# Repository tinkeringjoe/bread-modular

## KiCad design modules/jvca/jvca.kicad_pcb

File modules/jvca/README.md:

# JVCA

JFET based VCA with bias and gain control.

## Usage

* We can control CV gain with the "CV GAIN" RV and minumum gain is 0.05 and maximum is 1.
* CV bias RV will change the CV bias from 1V to 3V range.
  * If it's 1V, audio is audible even with CV change.
  * If it's 3V, audio is not audible

* If we center the CV around 2V, 500mv amplitude is enough to cut through the audio.
* But we can play with these values to get interesting results

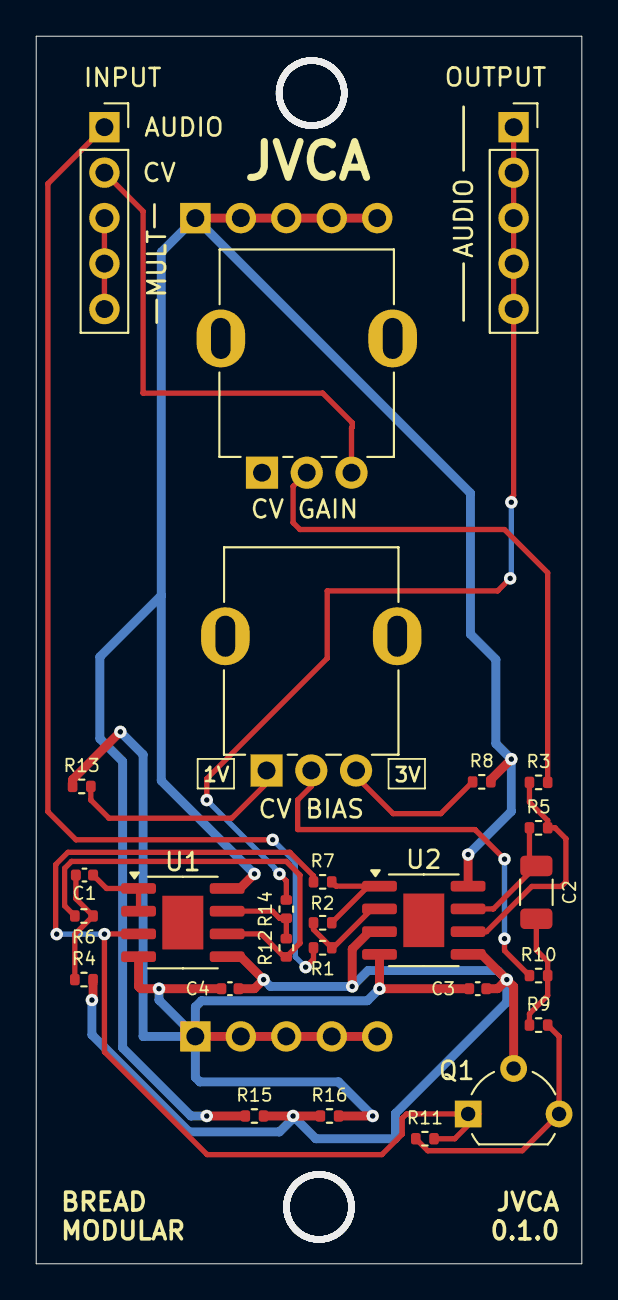
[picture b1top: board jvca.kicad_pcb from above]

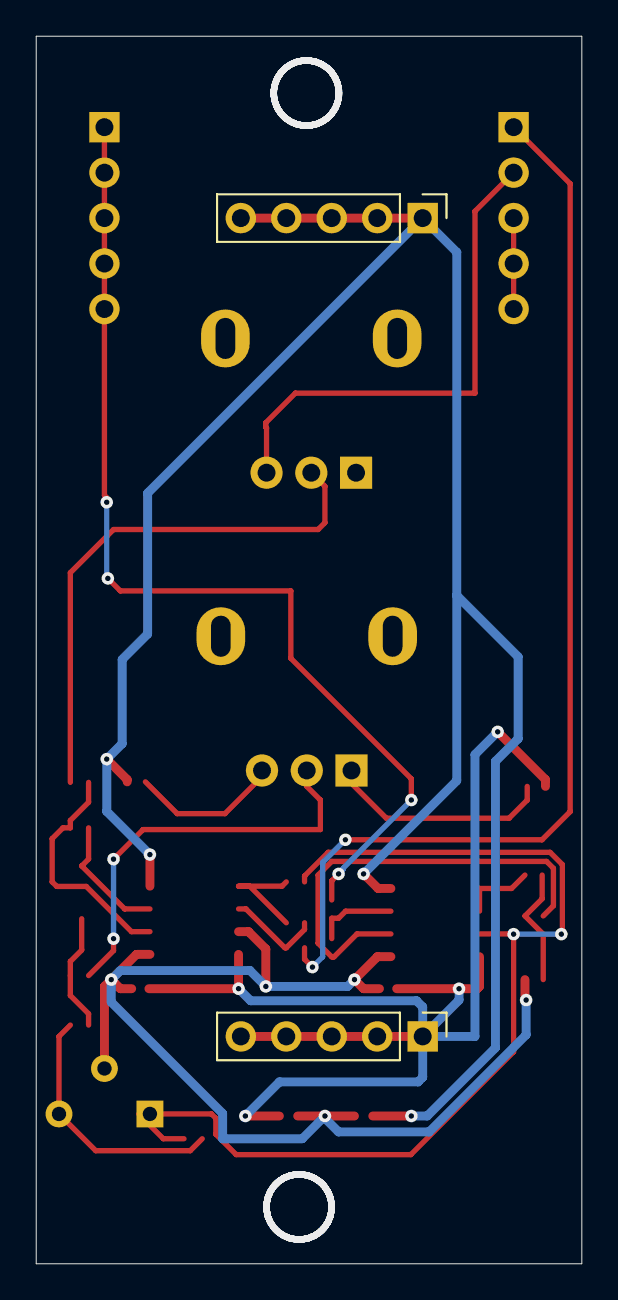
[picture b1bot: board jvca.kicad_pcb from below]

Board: 2 copper layers, 30.5 x 68.6 mm, 29 parts (2 on the bottom side), 22 nets.

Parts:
5V1: Conn_01x05_Pin; PinHeader_1x05_P2.54mm_Vertical
C1, C3, C4: 0.1uf; C_0402_1005Metric
C2: 4.7uf; C_1206_3216Metric
CV BIAS: 1k; Potentiometer_RV09
CV GAIN: 1M; Potentiometer_RV09
GND1: Conn_01x05_Pin; PinHeader_1x05_P2.54mm_Vertical
INPUT: Conn_01x05_Socket; PinSocket_1x05_P2.54mm_Vertical
OUTPUT: Conn_01x05_Socket; PinSocket_1x05_P2.54mm_Vertical
Q1: 2N5457; TO-92L_Wide
R1, R12: 200k; R_0402_1005Metric
R2, R6: 22k; R_0402_1005Metric
R3, R5: 51k; R_0402_1005Metric
R4, R7, R10: 100k; R_0402_1005Metric
R8: 2k; R_0402_1005Metric
R9, R11: 1M; R_0402_1005Metric
R13, R14, R15, R16: 1k; R_0402_1005Metric
U1, U2: MCP6002-xSN; SOIC-8-1EP_3.9x4.9mm_P1.27mm_EP2.29x3mm

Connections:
+2.5V: C3.2, C4.2, Q1.2 (S), R4.2, R15.2, R16.1, U1.5 (+), U2.3 (+), U2.5 (+)
+5V: 5V1.1, 5V1.2, 5V1.3, 5V1.4, 5V1.5, R8.2, R15.1, U1.8 (V+), U2.8 (V+)
CV: CV GAIN.3, INPUT.2
GND: C3.1, C4.1, GND1.1, GND1.2, GND1.3, GND1.4, GND1.5, R13.1, R16.2, U1.4 (V-), U2.4 (V-)
JFET_CV: C2.2, R9.1, R10.2
JFET_OUT: Q1.1 (D), R7.1, R11.2, U1.3 (+)
unnamed: C1.2, R4.1, R6.1
unnamed: C2.1, R5.1, U2.7
unnamed: INPUT.3, INPUT.4, INPUT.5
unnamed: Q1.3 (G), R9.2, R11.1
unnamed: R2.1, R7.2, U2.1
unnamed: CV GAIN.2, R3.2
unnamed: CV BIAS.3, R8.1
unnamed: CV BIAS.2, R10.1
unnamed: R12.2, R14.1, U1.7
unnamed: CV BIAS.1, R13.2
unnamed: C1.1, U1.1, U1.2 (-)
unnamed: R6.2, R12.1, U1.6 (-)
unnamed: R1.1, R2.2, U2.2 (-)
unnamed: R3.1, R5.2, U2.6 (-)
V_IN: INPUT.1, R1.2
V_OUT: OUTPUT.1, OUTPUT.2, OUTPUT.3, OUTPUT.4, OUTPUT.5, R14.2

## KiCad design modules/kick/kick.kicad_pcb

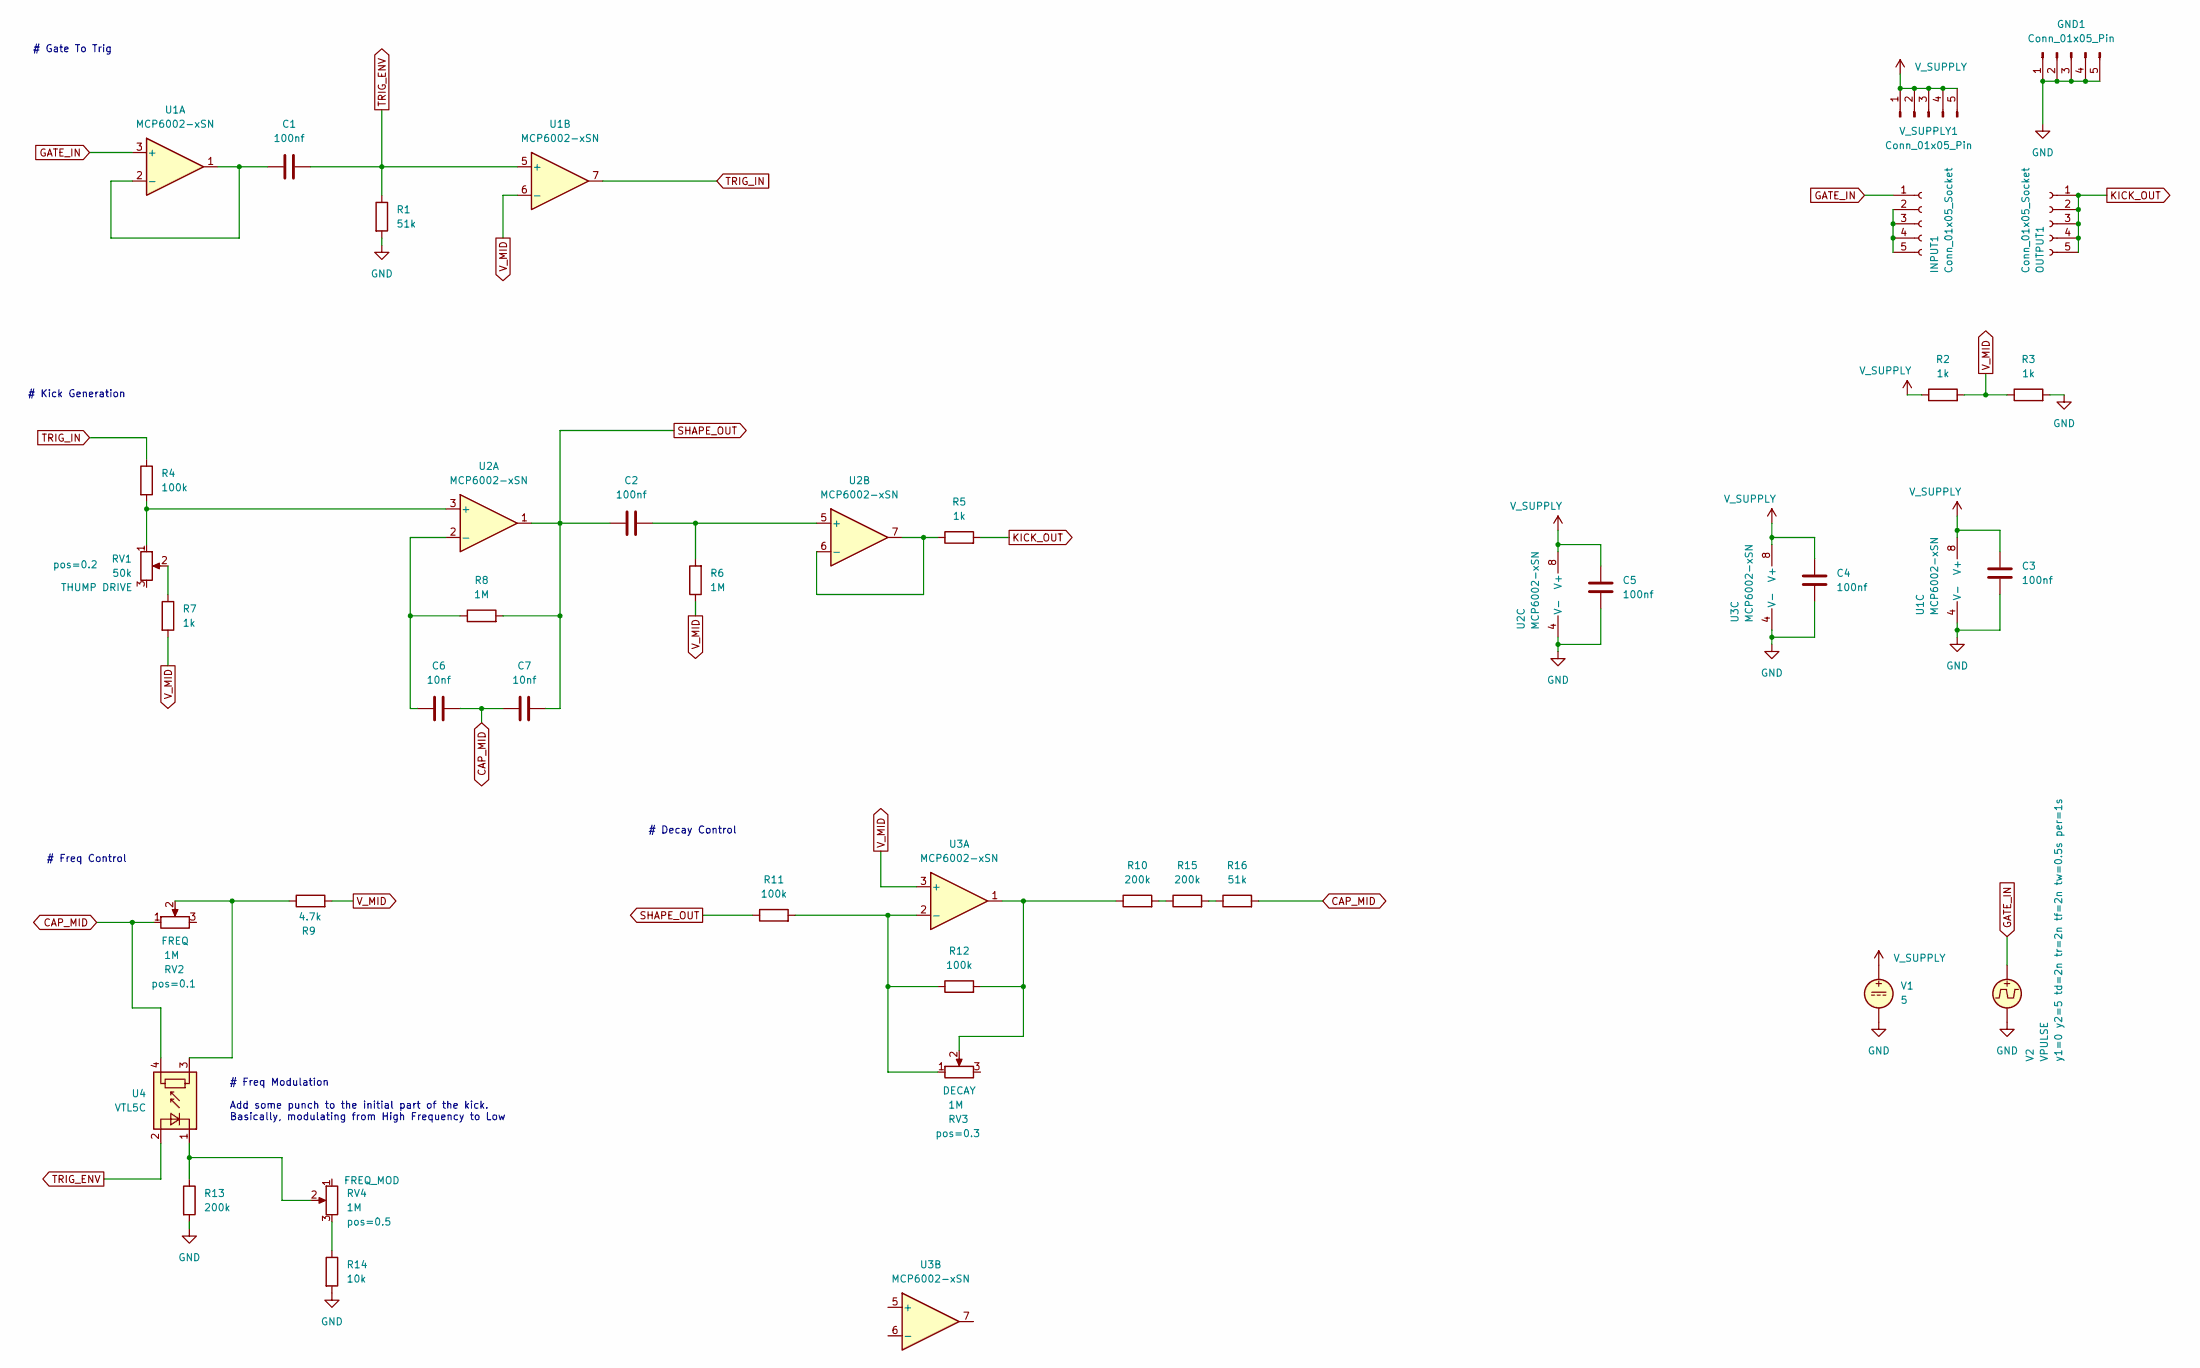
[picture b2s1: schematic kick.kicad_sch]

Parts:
C1, C2, C3, C4, C5: 100nf; C_0402_1005Metric
C6, C7: 10nf; C_0402_1005Metric
GND1: Conn_01x05_Pin; Power_Connector
INPUT1: Conn_01x05_Socket; PinSocket_1x05_P2.54mm_Vertical
OUTPUT1: Conn_01x05_Socket; PinSocket_1x05_P2.54mm_Vertical
R1, R16: 51k; R_0402_1005Metric
R2, R3, R5, R7: 1k; R_0402_1005Metric
R4, R11, R12: 100k; R_0402_1005Metric
R6, R8: 1M; R_0402_1005Metric
R9: 4.7k; R_0402_1005Metric
R10, R13, R15: 200k; R_0402_1005Metric
R14: 10k; R_0402_1005Metric
RV1: 50k; Potentiometer_RV09
RV2, RV3, RV4: 1M; Potentiometer_RV09
U1, U2, U3: MCP6002-xSN; SOIC-8-1EP_3.9x4.9mm_P1.27mm_EP2.29x3mm
U4: VTL5C
V1: 5
V2: VPULSE
V_SUPPLY1: Conn_01x05_Pin; Power_Connector

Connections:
CAP_MID: C6.2, C7.1, R16.2, RV2.1, U4.4
GATE_IN: INPUT1.1, U1.3 (+), V2.1
GND: C3.2, C4.2, C5.2, GND1.1, GND1.2, GND1.3, GND1.4, GND1.5, R1.2, R3.2, R13.2, R14.2, U1.4 (V-), U2.4 (V-), U3.4 (V-), V1.2, V2.2
KICK_OUT: OUTPUT1.1, OUTPUT1.2, OUTPUT1.3, OUTPUT1.4, OUTPUT1.5, R5.2
unnamed: INPUT1.2, INPUT1.3, INPUT1.4, INPUT1.5
unnamed: R7.1, RV1.2
unnamed: R9.1, RV2.2, U4.3
unnamed: R10.1, R12.2, RV3.2, U3.1
unnamed: R10.2, R15.1
unnamed: R14.1, RV4.3
unnamed: R15.2, R16.1
unnamed: C1.1, U1.1, U1.2 (-)
unnamed: R4.2, RV1.1, U2.3 (+)
unnamed: C6.1, R8.1, U2.2 (-)
unnamed: C2.2, R6.2, U2.5 (+)
unnamed: R5.1, U2.6 (-), U2.7
unnamed: R11.2, R12.1, RV3.1, U3.2 (-)
unnamed: R13.1, RV4.2, U4.1 (-)
SHAPE_OUT: C2.1, C7.2, R8.2, R11.1, U2.1
TRIG_ENV: C1.2, R1.1, U1.5 (+), U4.2 (+)
TRIG_IN: R4.1, U1.7
V_MID: R2.2, R3.1, R6.1, R7.2, R9.2, U1.6 (-), U3.3 (+)
V_SUPPLY: C3.1, C4.1, C5.1, R2.1, U1.8 (V+), U2.8 (V+), U3.8 (V+), V1.1, V_SUPPLY1.1, V_SUPPLY1.2, V_SUPPLY1.3, V_SUPPLY1.4, V_SUPPLY1.5

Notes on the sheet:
# Decay Control
# Gate To Trig
# Freq Control
# Kick Generation
# Freq Modulation Add some punch to the initial part of the kick. Basically, modulating from High Frequency to Low

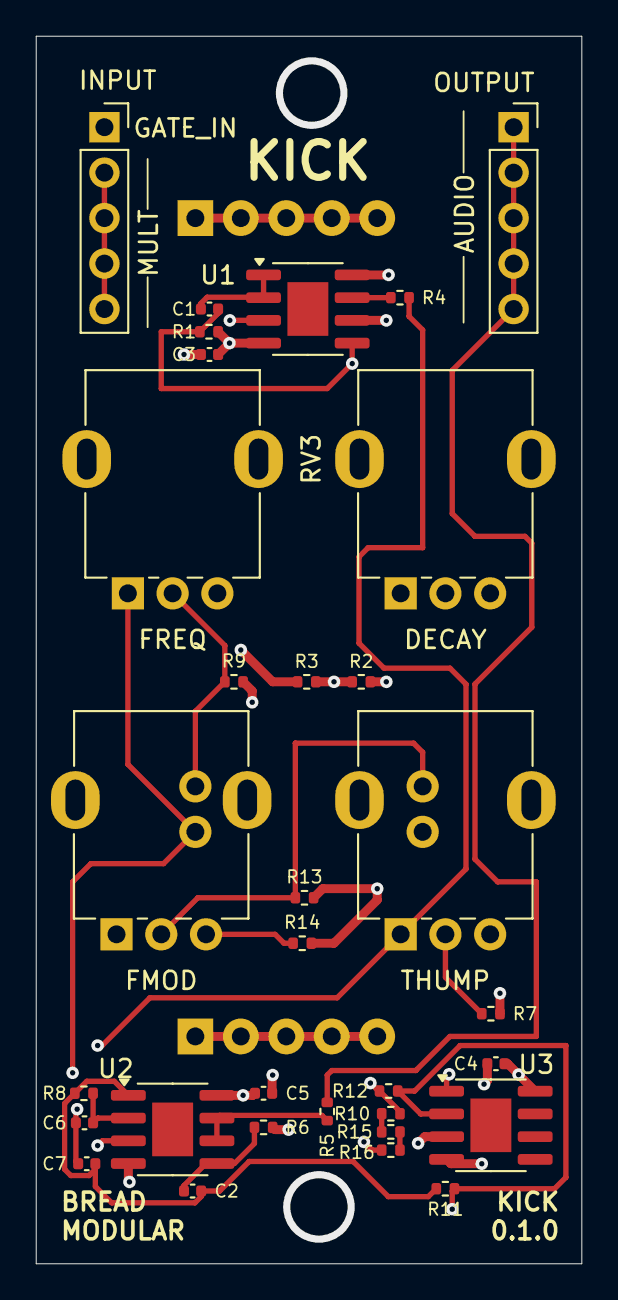
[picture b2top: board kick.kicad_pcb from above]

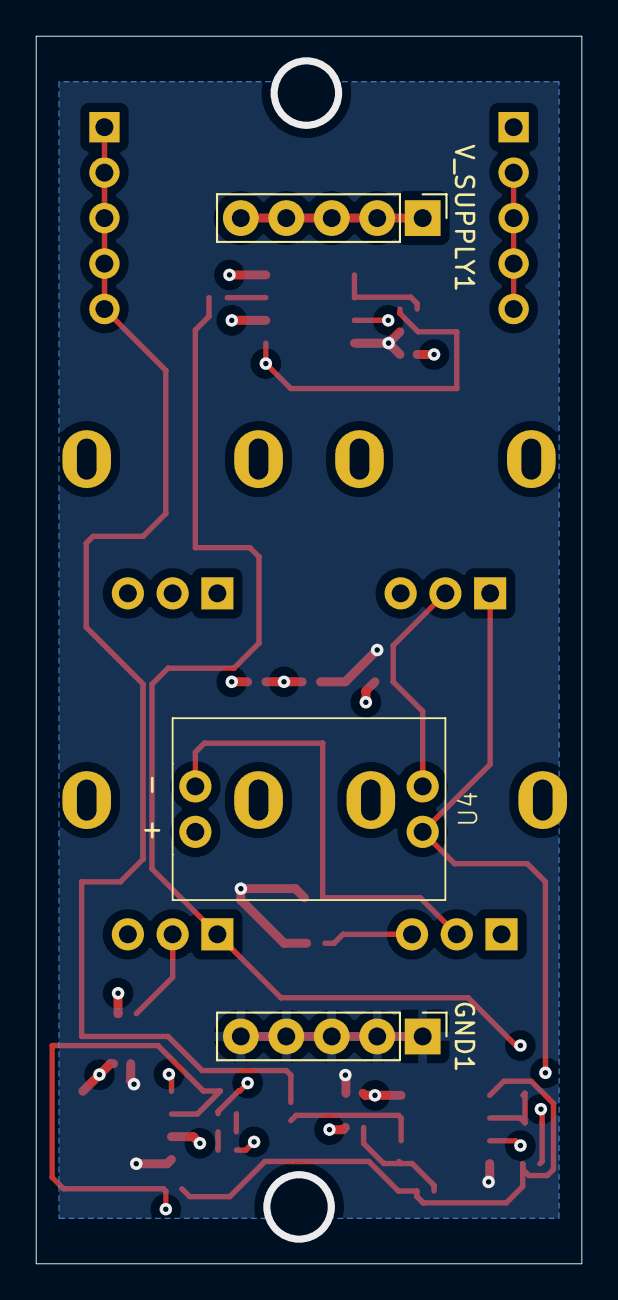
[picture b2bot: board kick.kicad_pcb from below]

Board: 4 copper layers, 30.5 x 68.6 mm, 35 parts (3 on the bottom side), 23 nets.

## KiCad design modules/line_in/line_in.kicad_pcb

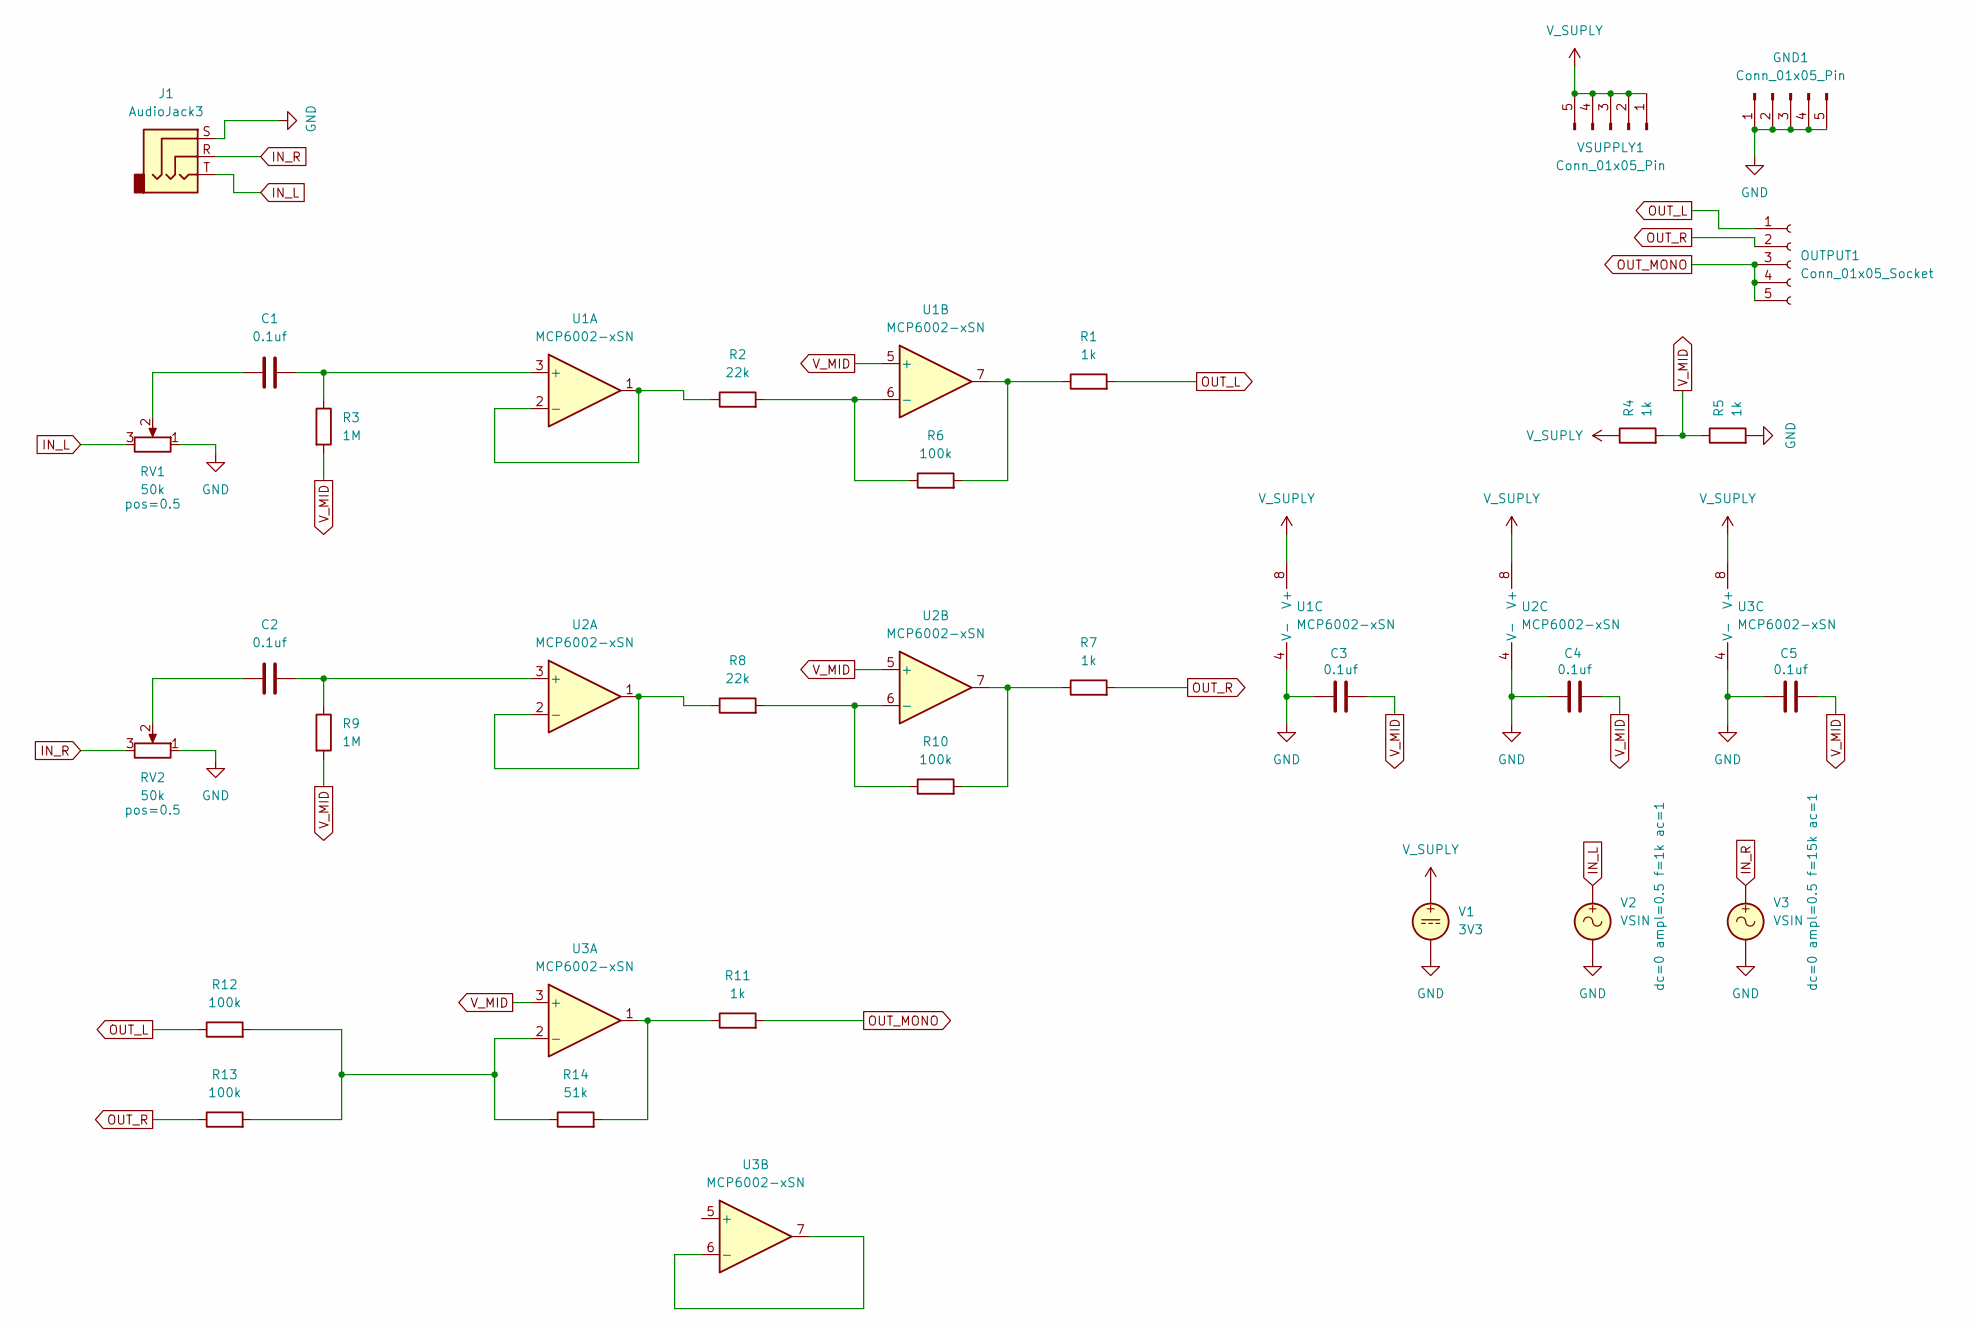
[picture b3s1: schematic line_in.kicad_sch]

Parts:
C1, C2, C3, C4, C5: 0.1uf; C_0402_1005Metric
GND1: Conn_01x05_Pin; Power_Connector
J1: AudioJack3; Jack_3.5mm_QingPu_WQP-PJ366ST_Vertical
OUTPUT1: Conn_01x05_Socket; PinSocket_1x05_P2.54mm_Vertical
R1, R4, R5, R7, R11: 1k; R_0402_1005Metric
R2, R8: 22k; R_0402_1005Metric
R3, R9: 1M; R_0402_1005Metric
R6, R10, R12, R13: 100k; R_0402_1005Metric
R14: 51k; R_0402_1005Metric
RV1, RV2: 50k; Potentiometer_RV09
U1, U2, U3: MCP6002-xSN; SOIC-8-1EP_3.9x4.9mm_P1.27mm_EP2.29x3mm
V1: 3V3
V2, V3: VSIN
VSUPPLY1: Conn_01x05_Pin; Power_Connector

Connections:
GND: C3.1, C4.1, C5.1, GND1.1, GND1.2, GND1.3, GND1.4, GND1.5, J1.S, R5.2, RV1.1, RV2.1, U1.4 (V-), U2.4 (V-), U3.4 (V-), V1.2, V2.2, V3.2
IN_L: J1.T, RV1.3, V2.1
IN_R: J1.R, RV2.3, V3.1
unnamed: C1.1, RV1.2
unnamed: C2.1, RV2.2
unnamed: R1.1, R6.2, U1.7
unnamed: R7.1, R10.2, U2.7
unnamed: R11.1, R14.2, U3.1
unnamed: C1.2, R3.1, U1.3 (+)
unnamed: R2.1, U1.1, U1.2 (-)
unnamed: R2.2, R6.1, U1.6 (-)
unnamed: C2.2, R9.1, U2.3 (+)
unnamed: R8.1, U2.1, U2.2 (-)
unnamed: R8.2, R10.1, U2.6 (-)
unnamed: R12.2, R13.2, R14.1, U3.2 (-)
unnamed: U3.6 (-), U3.7
OUT_L: OUTPUT1.1, R1.2, R12.1
OUT_MONO: OUTPUT1.3, OUTPUT1.4, OUTPUT1.5, R11.2
OUT_R: OUTPUT1.2, R7.2, R13.1
V_MID: C3.2, C4.2, C5.2, R3.2, R4.2, R5.1, R9.2, U1.5 (+), U2.5 (+), U3.3 (+)
V_SUPLY: R4.1, U1.8 (V+), U2.8 (V+), U3.8 (V+), V1.1, VSUPPLY1.1, VSUPPLY1.2, VSUPPLY1.3, VSUPPLY1.4, VSUPPLY1.5

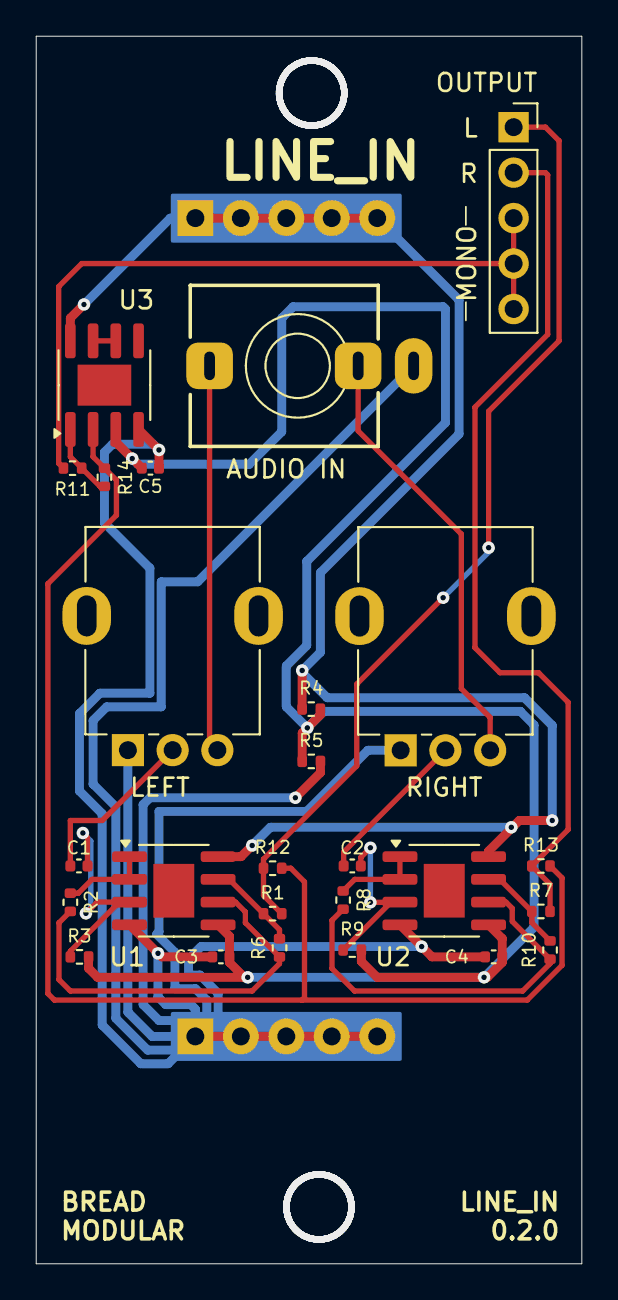
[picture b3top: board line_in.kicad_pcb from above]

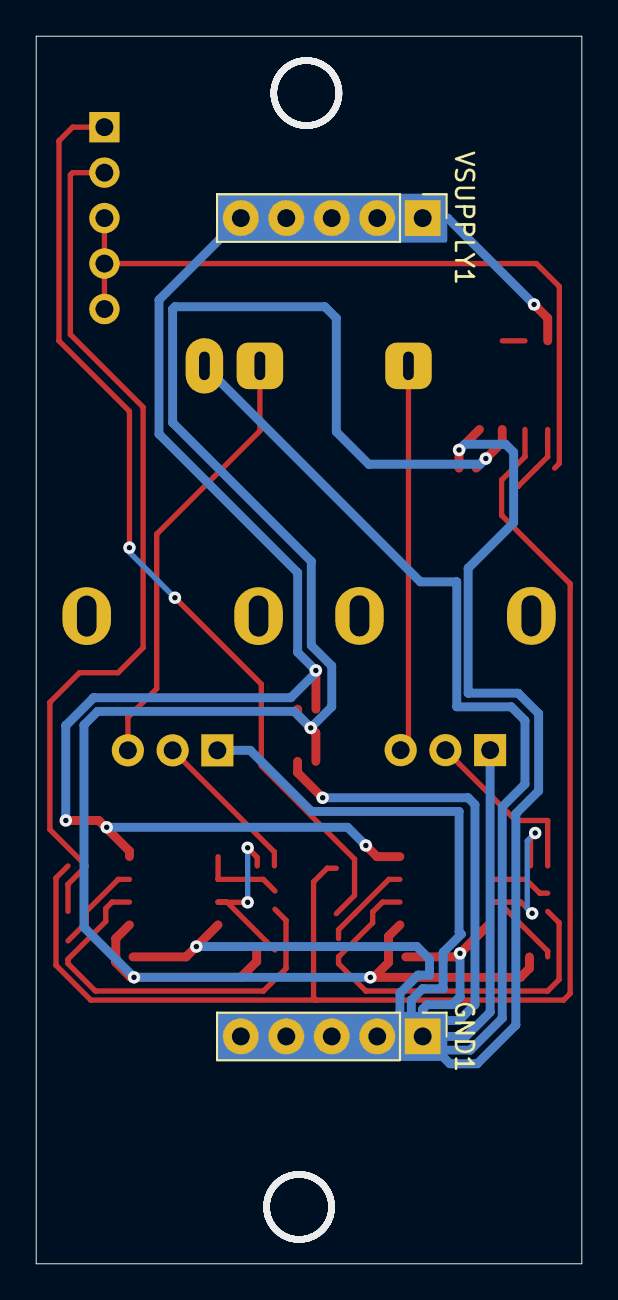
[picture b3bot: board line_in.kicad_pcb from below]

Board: 2 copper layers, 30.5 x 68.6 mm, 28 parts (2 on the bottom side), 21 nets.

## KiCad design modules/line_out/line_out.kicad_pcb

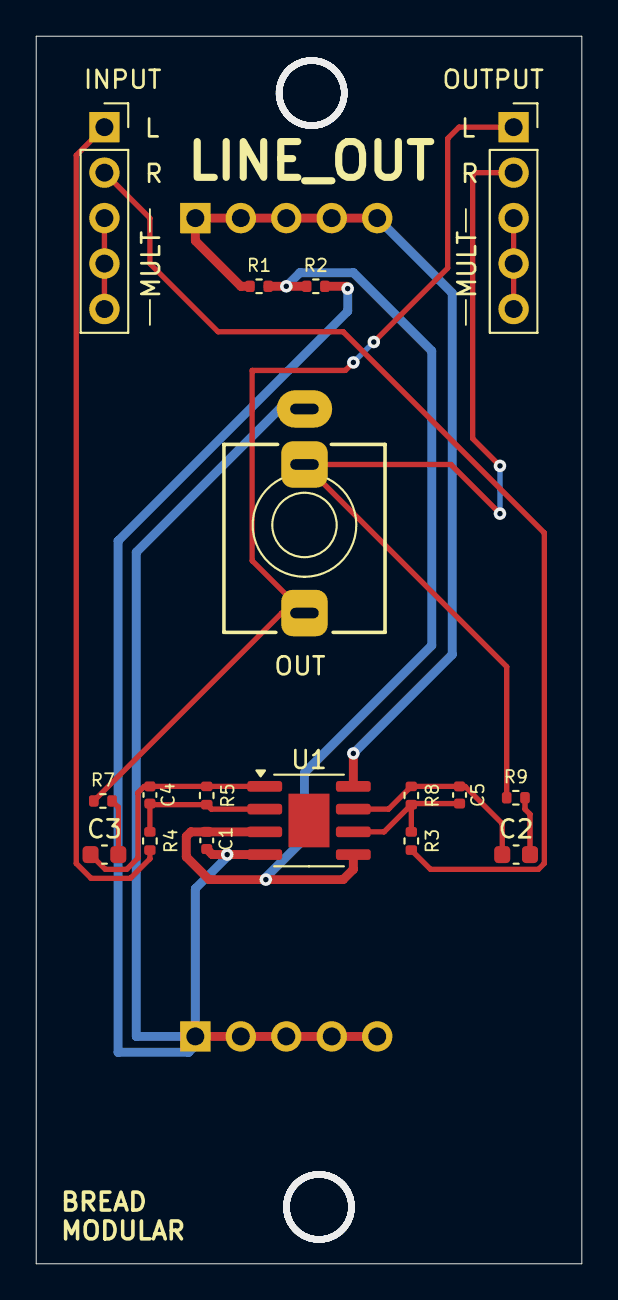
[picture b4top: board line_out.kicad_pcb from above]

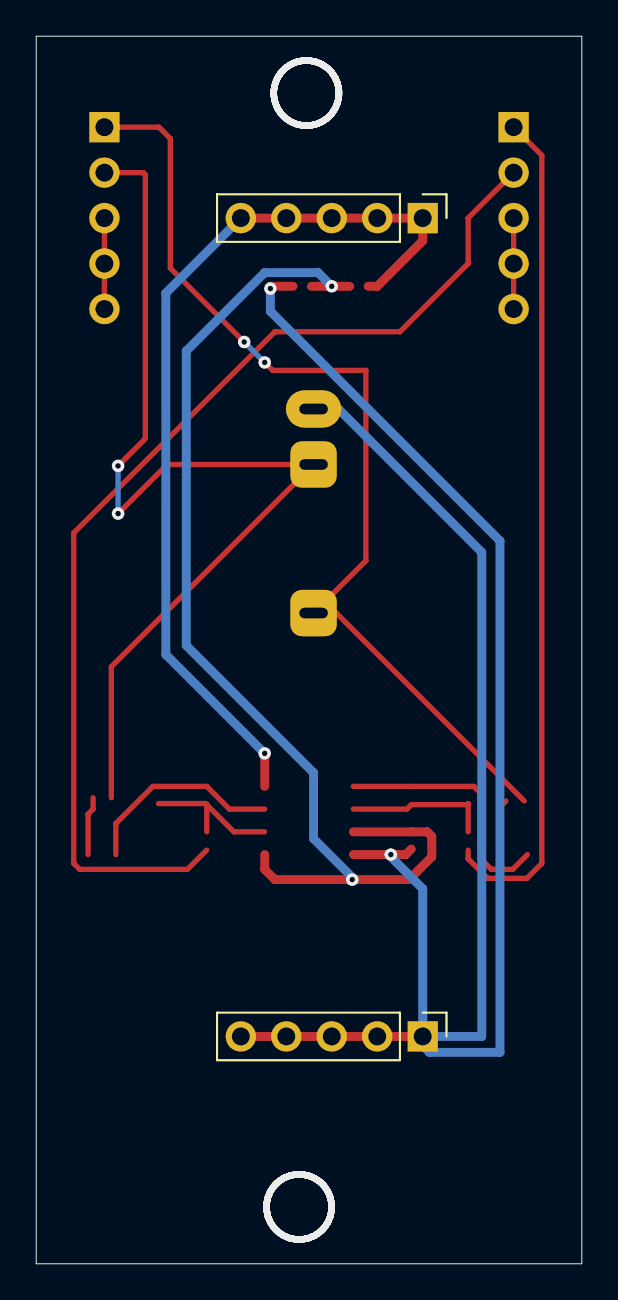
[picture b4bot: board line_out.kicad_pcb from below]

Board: 2 copper layers, 30.5 x 68.6 mm, 19 parts (2 on the bottom side), 15 nets.

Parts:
5V1: Conn_01x05_Pin; PinHeader_1x05_P2.54mm_Vertical
C1: 0.1uf; C_0402_1005Metric
C2, C3: 2.2uf; C_0603_1608Metric
C4, C5: 100pf; C_0402_1005Metric
GND1: Conn_01x05_Pin; PinHeader_1x05_P2.54mm_Vertical
INPUT: Conn_01x05_Socket; PinSocket_1x05_P2.54mm_Vertical
OUT: AudioJack3; Jack_3.5mm_QingPu_WQP-PJ366ST_Vertical
OUTPUT: Conn_01x05_Socket; PinSocket_1x05_P2.54mm_Vertical
R1, R2, R7, R9: 1k; R_0402_1005Metric
R3, R4: 100k; R_0402_1005Metric
R5, R8: 33k; R_0402_1005Metric
U1: TL072; SOIC-8-1EP_3.9x4.9mm_P1.27mm_EP2.29x3mm

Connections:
+2.5V: C1.2, R1.2, R2.1, U1.3 (+), U1.5 (+)
+5V: 5V1.1, 5V1.2, 5V1.3, 5V1.4, 5V1.5, R1.1, U1.8 (V+)
GND: C1.1, GND1.1, GND1.2, GND1.3, GND1.4, GND1.5, OUT.S, R2.2, U1.4 (V-)
IN_L: INPUT.1, R4.2
IN_R: INPUT.2, R3.2
unnamed: C2.1, C5.1, R8.1, U1.7
unnamed: C2.2, R9.2
unnamed: C3.1, C4.1, R5.1, U1.1
unnamed: C3.2, R7.2
unnamed: INPUT.3, INPUT.4, INPUT.5
unnamed: OUTPUT.3, OUTPUT.4, OUTPUT.5
unnamed: C4.2, R4.1, R5.2, U1.2 (-)
unnamed: C5.2, R3.1, R8.2, U1.6 (-)
OUT_L: OUT.T, OUTPUT.1, R7.1
OUT_R: OUT.R, OUTPUT.2, R9.1

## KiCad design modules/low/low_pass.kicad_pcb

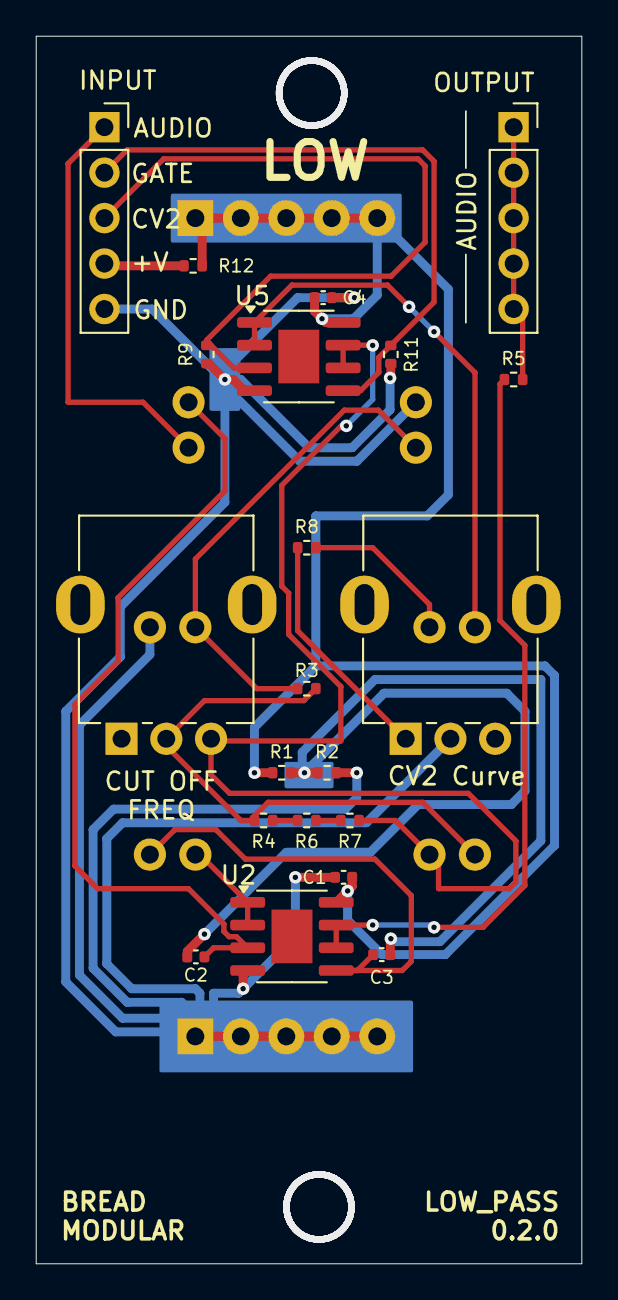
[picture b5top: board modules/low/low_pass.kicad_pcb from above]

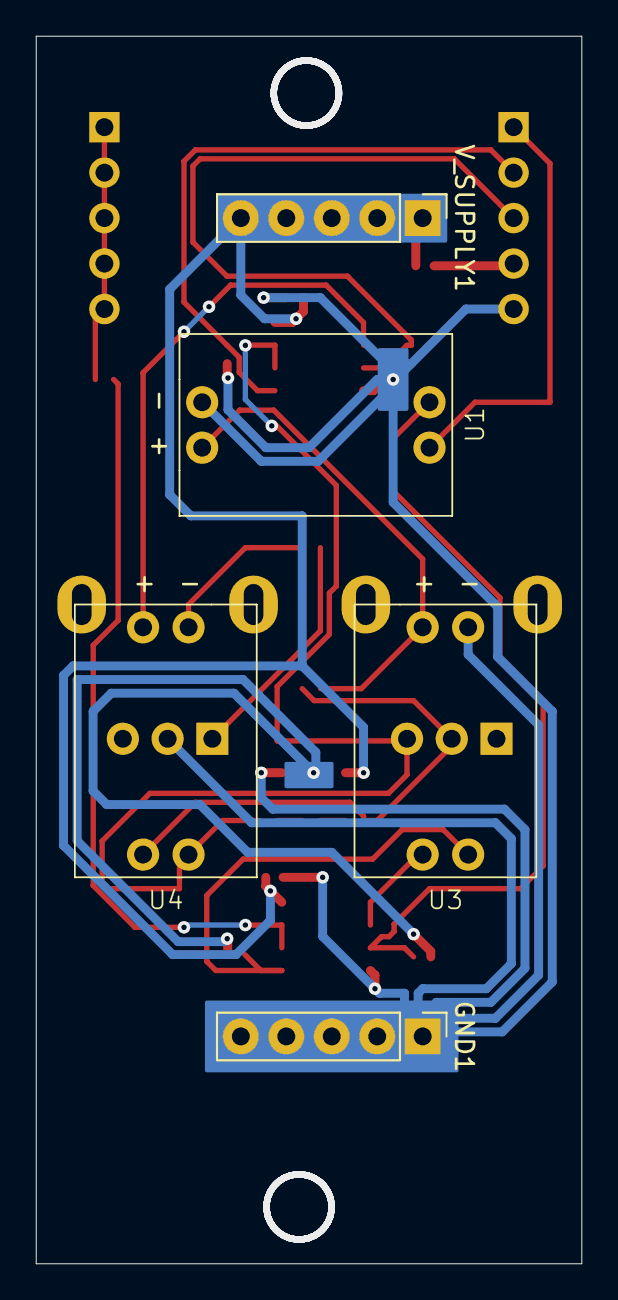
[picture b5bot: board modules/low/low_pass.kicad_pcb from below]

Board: 2 copper layers, 30.5 x 68.6 mm, 26 parts (5 on the bottom side), 20 nets.

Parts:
C1, C4: 0.1uf; C_0402_1005Metric
C2, C3: 10nf; C_0402_1005Metric
GND1: Conn_01x05_Pin; Power_Connector
INPUT1: Conn_01x05_Socket; PinSocket_1x05_P2.54mm_Vertical
OUTPUT1: Conn_01x05_Socket; PinSocket_1x05_P2.54mm_Vertical
R1, R2, R5: 1k; R_0402_1005Metric
R3, R8: 560; R_0402_1005Metric
R4, R6, R7: 200k; R_0402_1005Metric
R9, R11: 1M; R_0402_1005Metric
R12: 10k; R_0402_1005Metric
RV1, RV2: 1M; Potentiometer_RV09
U1, U3, U4: VTL5C
U2, U5: MCP6002-xSN; SOIC-8-1EP_3.9x4.9mm_P1.27mm_EP2.29x3mm
V_SUPPLY1: Conn_01x05_Pin; Power_Connector

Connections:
AUDIO_IN: INPUT1.1, U1.4
AUDIO_OUT: OUTPUT1.1, OUTPUT1.2, OUTPUT1.3, OUTPUT1.4, OUTPUT1.5, R5.2
CUT_OFF_CV: INPUT1.3, R9.2, U5.3 (+)
GATE_CV: INPUT1.2, R11.2, U5.5 (+)
GND: C1.2, C4.2, GND1.1, GND1.2, GND1.3, GND1.4, GND1.5, INPUT1.5, R2.2, R9.1, R11.1, RV2.2, U1.1 (-), U2.4 (V-), U3.1 (-), U5.4 (V-)
unnamed: INPUT1.4, R12.2
unnamed: R3.2, R4.2, RV1.2, U4.4
unnamed: R4.1, R6.2
unnamed: R6.1, R7.2
unnamed: R8.1, RV2.1
unnamed: R3.1, U1.2 (+), U3.2 (+)
unnamed: C2.1, U1.3, U2.3 (+)
unnamed: U2.1, U2.2 (-), U3.4
unnamed: C3.1, U2.5 (+), U3.3
unnamed: R5.1, U2.6 (-), U2.7
unnamed: U4.2 (+), U5.1, U5.2 (-)
unnamed: R8.2, U4.1 (-)
unnamed: R7.1, RV1.3, U4.3, U5.6 (-), U5.7
V_MID: C2.2, C3.2, R1.2, R2.1
V_SUPPLY: C1.1, C4.1, R1.1, R12.1, U2.8 (V+), U5.8 (V+), V_SUPPLY1.1, V_SUPPLY1.2, V_SUPPLY1.3, V_SUPPLY1.4, V_SUPPLY1.5

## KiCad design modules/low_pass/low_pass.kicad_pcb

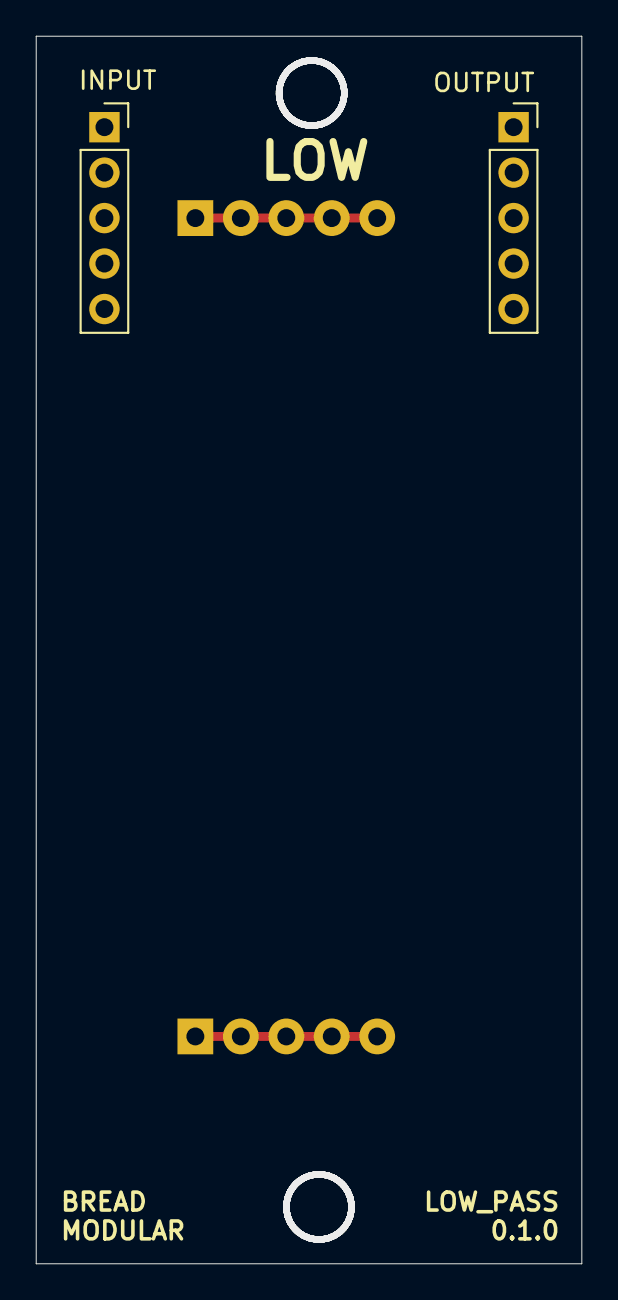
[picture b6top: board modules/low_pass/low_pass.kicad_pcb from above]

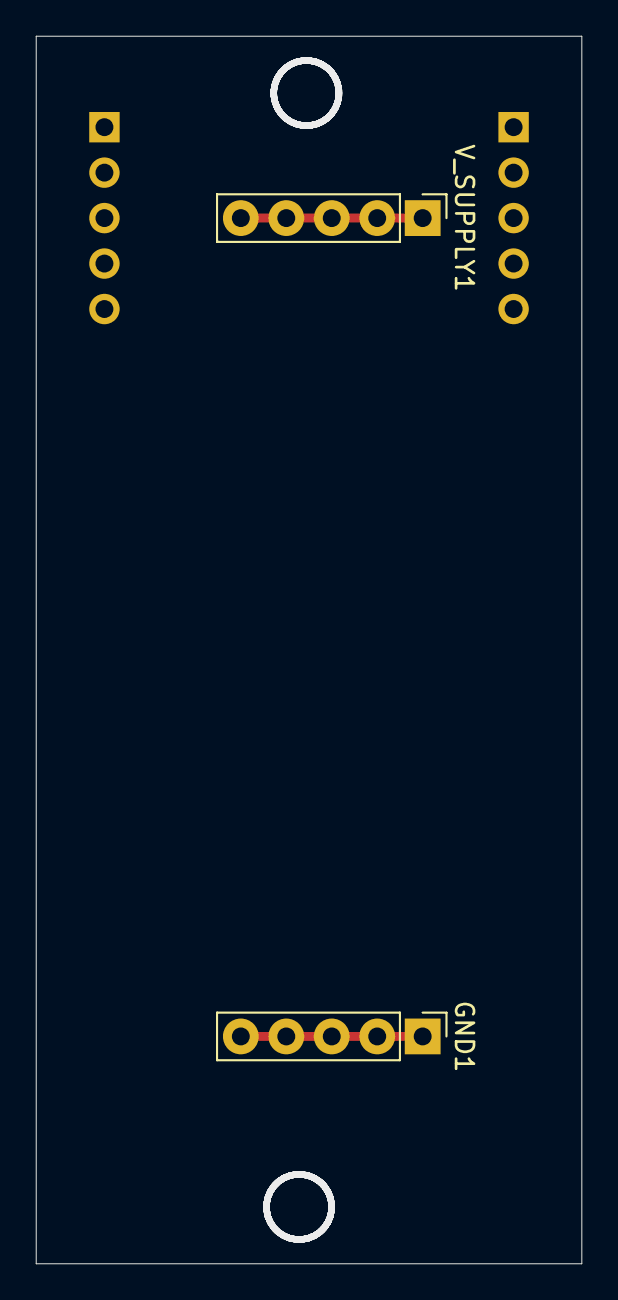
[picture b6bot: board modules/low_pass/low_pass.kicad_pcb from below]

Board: 2 copper layers, 30.5 x 68.6 mm, 4 parts (2 on the bottom side), 2 nets.

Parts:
GND1: Conn_01x05_Pin; Power_Connector
INPUT1: Conn_01x05_Socket; PinSocket_1x05_P2.54mm_Vertical
OUTPUT1: Conn_01x05_Socket; PinSocket_1x05_P2.54mm_Vertical
V_SUPPLY1: Conn_01x05_Pin; Power_Connector

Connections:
GND: GND1.1, GND1.2, GND1.3, GND1.4, GND1.5
V_SUPPLY: V_SUPPLY1.1, V_SUPPLY1.2, V_SUPPLY1.3, V_SUPPLY1.4, V_SUPPLY1.5
